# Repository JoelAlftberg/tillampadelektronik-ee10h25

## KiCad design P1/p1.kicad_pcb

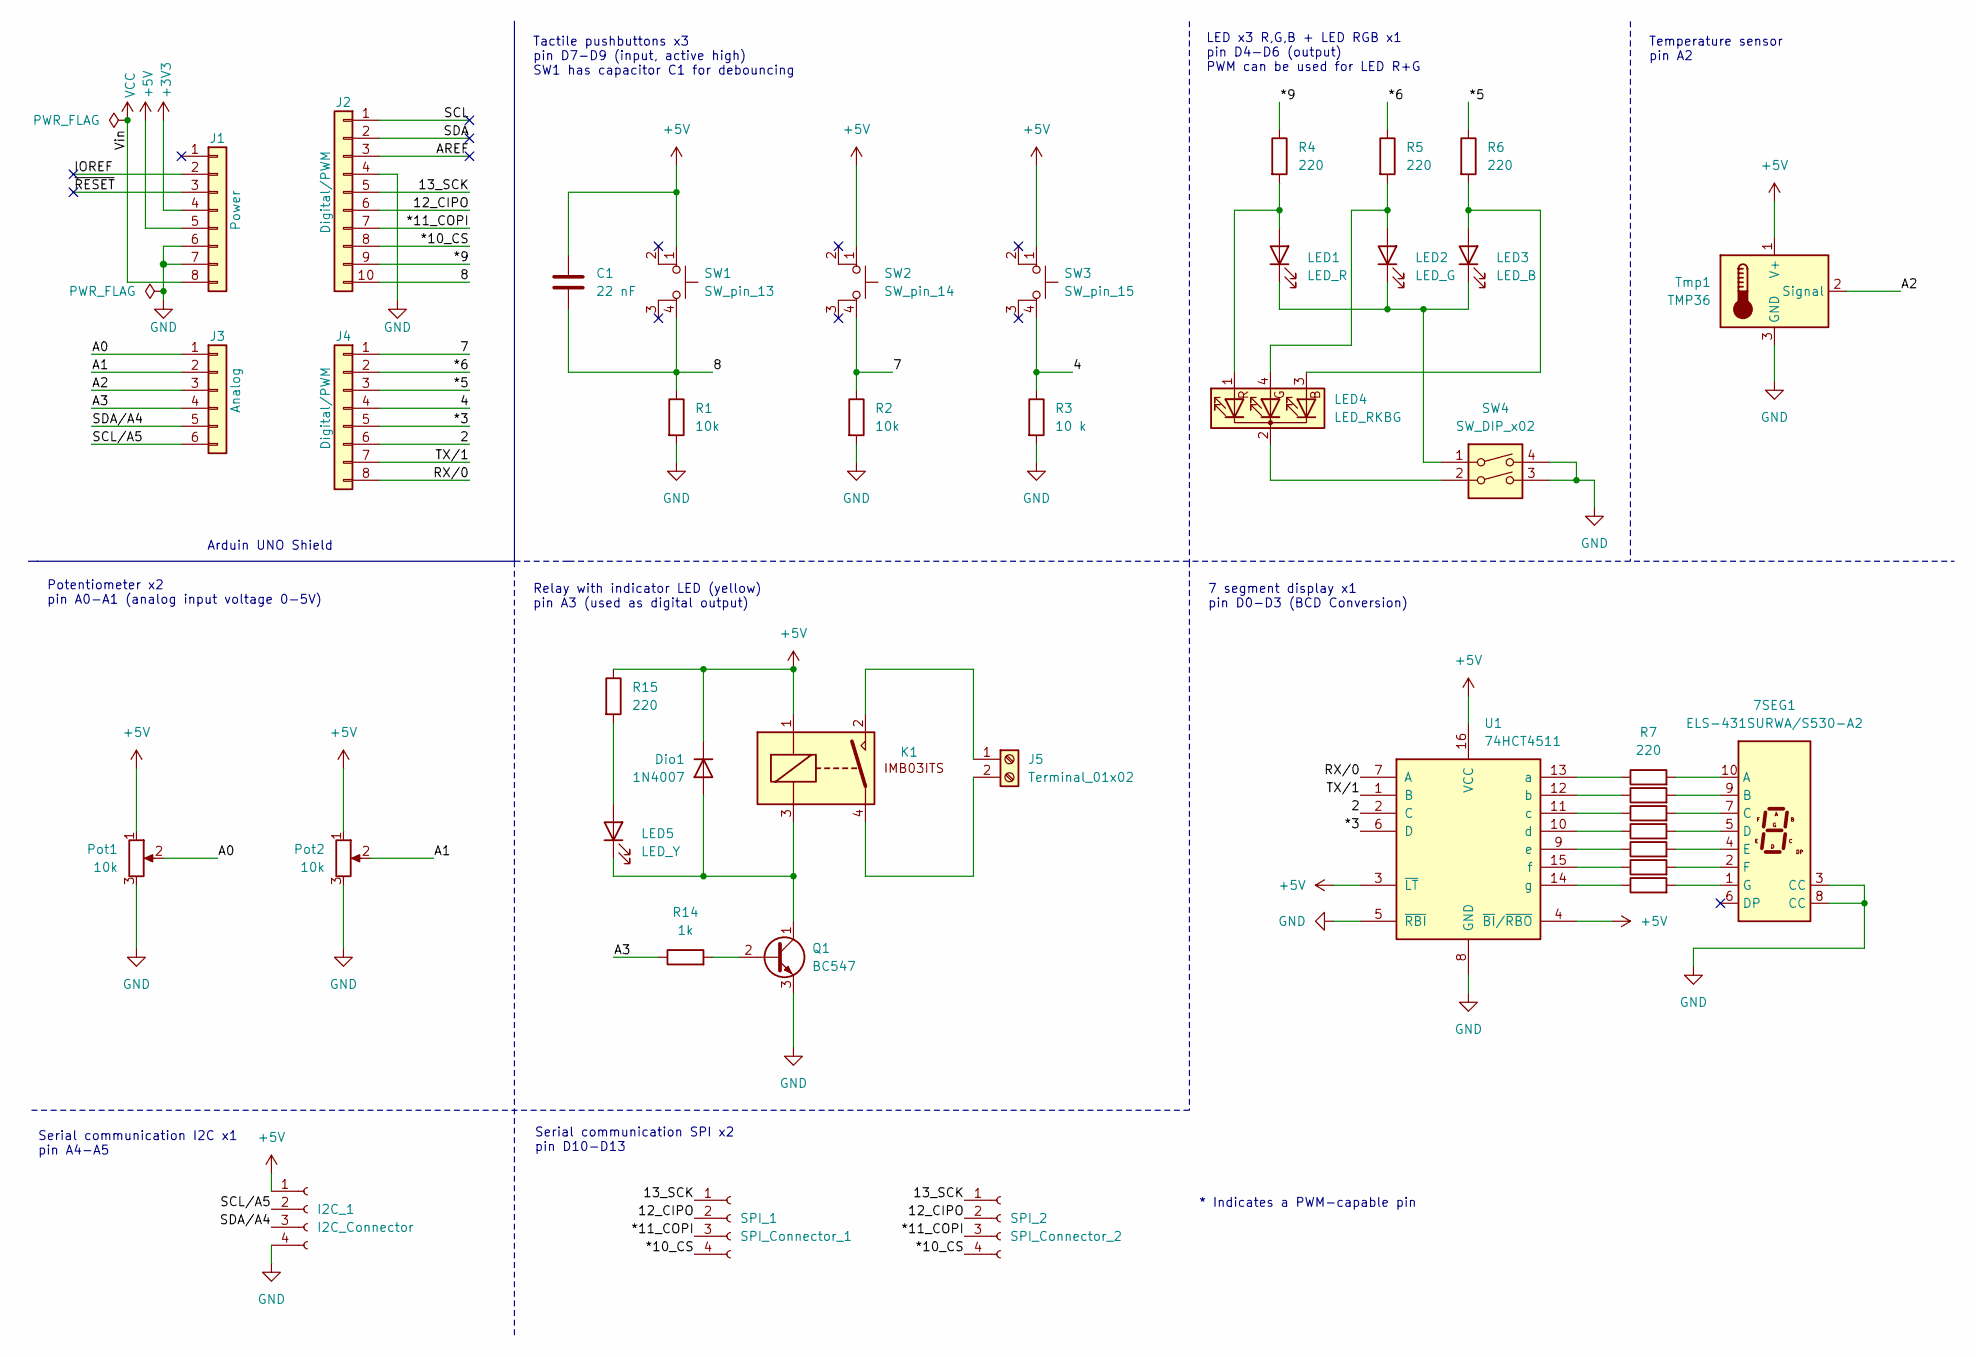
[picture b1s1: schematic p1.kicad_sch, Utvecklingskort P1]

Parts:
7SEG1: ELS-431SURWA/S530-A2; Sx39-1xxxxx
C1: 22 nF; C_Rect_L7.2mm_W2.5mm_P5.00mm_FKS2_FKP2_MKS2_MKP2
Dio1: 1N4007; D_DO-41_SOD81_P10.16mm_Horizontal
I2C_1: I2C_Connector; PinSocket_1x04_P2.00mm_Vertical
J1: Power; PinSocket_1x08_P2.54mm_Vertical
J2: Digital/PWM; PinSocket_1x10_P2.54mm_Vertical
J3: Analog; PinSocket_1x06_P2.54mm_Vertical
J4: Digital/PWM; PinSocket_1x08_P2.54mm_Vertical
J5: Terminal_01x02; TerminalBlock_Phoenix_MKDS-1,5-2-5.08_1x02_P5.08mm_Horizont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
K1: IMB03ITS
LED1: LED_R; LED_D5.0mm
LED2: LED_G; LED_D5.0mm
LED3: LED_B; LED_D5.0mm
LED4: LED_RKBG; LED_D5.0mm-4_RGB
LED5: LED_Y; LED_D5.0mm
Pot1, Pot2: 10k; Potentiometer_Piher_PT-10-V10_Vertical
Q1: BC547; TO-92L_Inline
R1, R2: 10k; R_Axial_DIN0207_L6.3mm_D2.5mm_P10.16mm_Horizontal
R3: 10 k; R_Axial_DIN0207_L6.3mm_D2.5mm_P10.16mm_Horizontal
R4, R5, R6, R7, R15: 220; R_Axial_DIN0207_L6.3mm_D2.5mm_P10.16mm_Horizontal
R8, R9, R10, R11, R12, R13: 220R; R_Axial_DIN0207_L6.3mm_D2.5mm_P10.16mm_Horizontal
R14: 1k; R_Axial_DIN0207_L6.3mm_D2.5mm_P10.16mm_Horizontal
SPI_1: SPI_Connector_1; PinSocket_1x04_P2.00mm_Vertical
SPI_2: SPI_Connector_2; PinSocket_1x04_P2.00mm_Vertical
SW1: SW_pin_13; RND_Tactile_Switch_THT
SW2: SW_pin_14; RND_Tactile_Switch_THT
SW3: SW_pin_15; RND_Tactile_Switch_THT
SW4: SW_DIP_x02; SW_DIP_SPSTx02_Slide_6.7x6.64mm_W7.62mm_P2.54mm_LowProfile
Tmp1: TMP36; TO-92_Inline
U1: 74HCT4511; DIP-16_W7.62mm

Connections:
+3V3: J1.4
+5V: C1.1, Dio1.1 (K), I2C_1.1, J1.5, K1.1, Pot1.1, Pot2.1, R15.1, SW1.1, SW2.1, SW3.1, Tmp1.1 (V+), U1.3 (~LT), U1.4 (~BI/~RBO), U1.16 (VCC)
/2: J4.6, U1.2 (C)
/4: J4.4, R3.1, SW3.4 (A)
/7: J4.1, R2.1, SW2.4 (A)
/8: C1.2, J2.10, R1.1, SW1.4 (A)
/12_CIPO: J2.6, SPI_1.2, SPI_2.2
/13_SCK: J2.5, SPI_1.1, SPI_2.1
/*3: J4.5, U1.6 (D)
/*5: J4.3, R6.1
/*6: J4.2, R5.1
/*9: J2.9, R4.1
/*10_CS: J2.8, SPI_1.4, SPI_2.4
/*11_COPI: J2.7, SPI_1.3, SPI_2.3
/A0: J3.1, Pot1.2
/A1: J3.2, Pot2.2
/A2: J3.3, Tmp1.2 (Signal)
/A3: J3.4, R14.1
/AREF: J2.3
/IOREF: J1.2
/RX/0: J4.8, U1.7 (A)
/SCL: J2.1
/SCL/A5: I2C_1.2, J3.6
/SDA: J2.2
/SDA/A4: I2C_1.3, J3.5
/TX/1: J4.7, U1.1 (B)
/~RESET: J1.3
GND: 7SEG1.3 (CC), 7SEG1.8 (CC), I2C_1.4, J1.6, J1.7, J2.4, Pot1.3, Pot2.3, Q1.3 (E), R1.2, R2.2, R3.2, SW4.3, SW4.4, Tmp1.3 (GND), U1.5 (~RBI), U1.8 (GND)
unnamed: 7SEG1.10 (A), R7.2
unnamed: 7SEG1.9 (B), R8.2
unnamed: 7SEG1.7 (C), R9.2
unnamed: 7SEG1.5 (D), R10.2
unnamed: 7SEG1.4 (E), R11.2
unnamed: 7SEG1.2 (F), R12.2
unnamed: 7SEG1.1 (G), R13.2
unnamed: Dio1.2 (A), K1.3, LED5.1 (K), Q1.1 (C)
unnamed: J5.1, K1.2
unnamed: J5.2, K1.4
unnamed: LED1.2 (A), LED4.1 (RA), R4.2
unnamed: LED1.1 (K), LED2.1 (K), LED3.1 (K), SW4.1
unnamed: LED2.2 (A), LED4.4 (GA), R5.2
unnamed: LED3.2 (A), LED4.3 (BA), R6.2
unnamed: LED4.2 (K), SW4.2
unnamed: LED5.2 (A), R15.2
unnamed: Q1.2 (B), R14.2
unnamed: R7.1, U1.13 (a)
unnamed: R8.1, U1.12 (b)
unnamed: R9.1, U1.11 (c)
unnamed: R10.1, U1.10 (d)
unnamed: R11.1, U1.9 (e)
unnamed: R12.1, U1.15 (f)
unnamed: R13.1, U1.14 (g)
VCC: J1.8

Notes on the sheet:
Temperature sensor pin A2
Tactile pushbuttons x3 pin D7-D9 (input, active high) SW1 has capacitor C1 for debouncing
LED x3 R,G,B + LED RGB x1 pin D4-D6 (output) PWM can be used for LED R+G
Serial communication I2C x1 pin A4-A5
Relay with indicator LED (yellow) pin A3 (used as digital output)
Arduin UNO Shield
Potentiometer x2 pin A0-A1 (analog input voltage 0-5V)
* Indicates a PWM-capable pin
Serial communication SPI x2 pin D10-D13
7 segment display x1 pin D0-D3 (BCD Conversion)

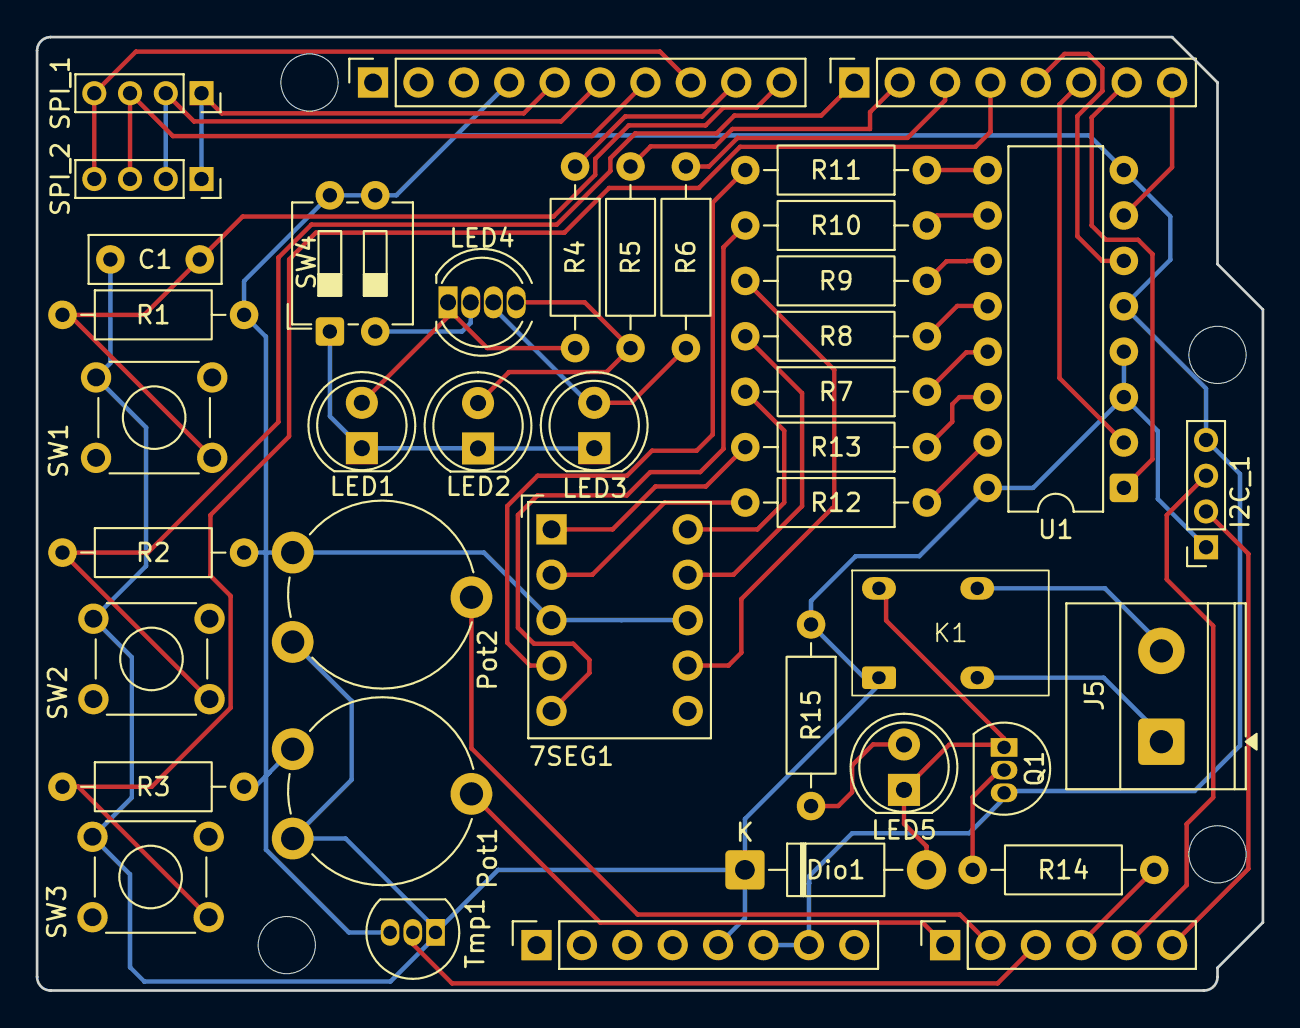
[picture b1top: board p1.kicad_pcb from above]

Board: 2 copper layers, 68.6 x 53.3 mm, 45 parts (0 on the bottom side), 46 nets.

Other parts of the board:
MH1, MH2, MH3, MH4: MountingHole_3.2mm

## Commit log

2025-09-10 Add L03
2025-09-11 Adds L03
2025-10-06 Updates PCB for P1
2025-10-13 Adds P1 finished proj
2025-10-17 Adds L12
2025-10-22 Adds P2
2025-10-23 Adds rounding and formatting data for P2
